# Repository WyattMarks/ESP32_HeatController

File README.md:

# ESP32_HeatController

This is a PID heat controller using the ESP32. The PCB and schematics are included, as well as the software used to run it. It's still a WIP, so expect changes.

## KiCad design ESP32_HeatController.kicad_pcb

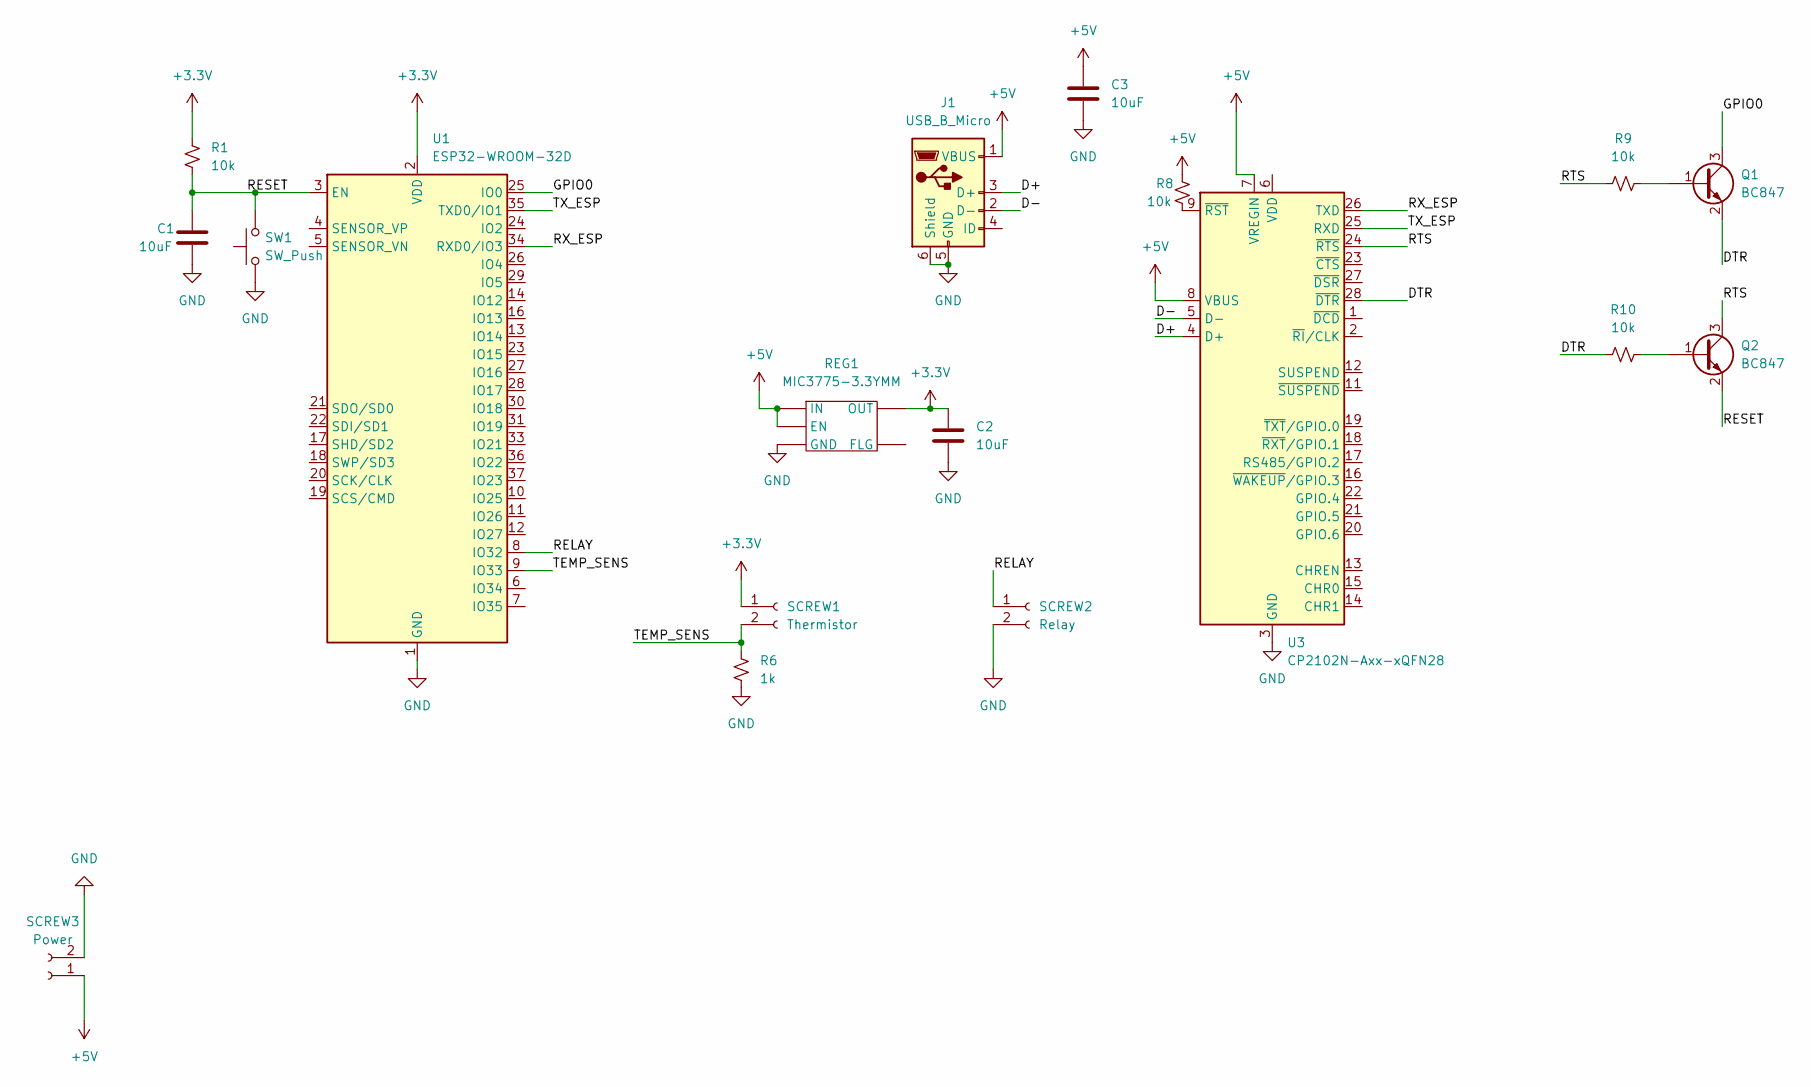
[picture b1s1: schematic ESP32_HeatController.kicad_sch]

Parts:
C1, C2, C3: 10uF; C_0603_1608Metric
J1: USB_B_Micro; USB_Micro-B_Amphenol_10104110_Horizontal
Q1, Q2: BC847; SOT-523
R1, R8, R9, R10: 10k; R_0603_1608Metric
R6: 1k; R_0603_1608Metric
REG1: MIC3775-3.3YMM; MSOP8-Reg
SCREW1: Thermistor; JWT_A3963_1x02_P3.96mm_Vertical
SCREW2: Relay; JWT_A3963_1x02_P3.96mm_Vertical
SCREW3: Power; JWT_A3963_1x02_P3.96mm_Vertical
SW1: SW_Push; SW_SPST_EVPBF
U1: ESP32-WROOM-32D; ESP32-WROOM-32
U3: CP2102N-Axx-xQFN28; QFN-28-1EP_5x5mm_P0.5mm_EP3.35x3.35mm

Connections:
+3V3: C2.1, R1.1, REG1.OUT, SCREW1.1, U1.2 (VDD)
+5V: C3.1, J1.1 (VBUS), R8.2, REG1.EN, REG1.IN, SCREW3.1, U3.7 (VREGIN), U3.8 (VBUS)
/D+: J1.3 (D+), U3.4 (D+)
/D-: J1.2 (D-), U3.5 (D-)
/DTR: Q1.2 (E), R10.1, U3.28 (~DTR)
/GPIO0: Q1.3 (C), U1.25 (IO0)
/RELAY: SCREW2.1, U1.8 (IO32)
/RESET: C1.1, Q2.2 (E), R1.2, SW1.2, U1.3 (EN)
/RTS: Q2.3 (C), R9.1, U3.24 (~RTS)
/RX_ESP: U1.34 (RXD0/IO3), U3.26 (TXD)
/TEMP_SENS: R6.1, SCREW1.2, U1.9 (IO33)
/TX_ESP: U1.35 (TXD0/IO1), U3.25 (RXD)
GND: C1.2, C2.2, C3.2, J1.5 (GND), J1.6 (Shield), R6.2, REG1.GND, SCREW2.2, SCREW3.2, SW1.1, U1.1 (GND), U1.15 (GND), U1.38 (GND), U1.39 (GND), U3.3 (GND), U3.29 (GND)
unnamed: Q1.1 (B), R9.2
unnamed: Q2.1 (B), R10.2
unnamed: R8.1, U3.9 (~RST)

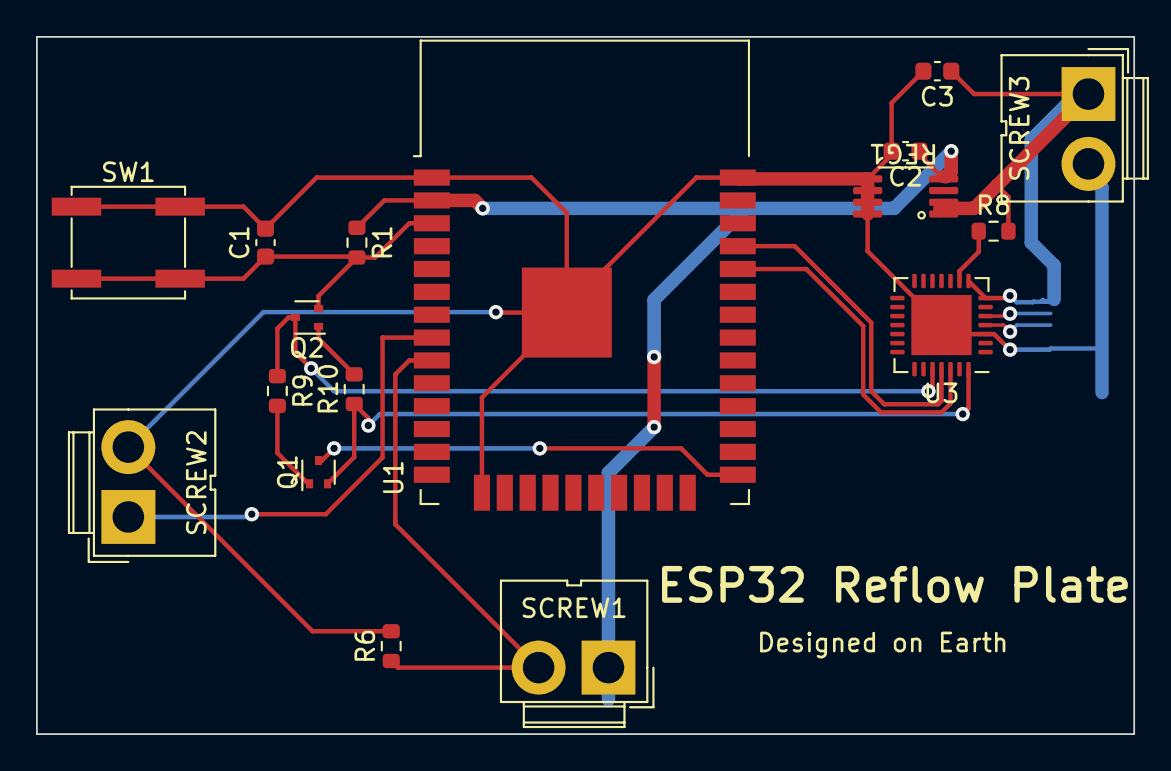
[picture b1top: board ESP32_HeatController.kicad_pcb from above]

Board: 2 copper layers, 61.0 x 38.7 mm, 18 parts (1 on the bottom side), 16 nets.

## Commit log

2022-02-03 Initial Commit to git
2022-02-03 Add temperature control
2022-02-03 Fix typo
2022-02-03 Fixed last typo
2022-02-03 Added an On/Off button
2022-02-03 Small button changes
2022-02-05 Fixed goal temp chart bug, fixed degree symbol
2022-02-05 Added 3D Model of the base
